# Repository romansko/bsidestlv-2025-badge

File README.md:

# BSidesTLV2025 Hardware CTF
Unlock the hidden secrets of the badge. What kind of secrets lie in waiting? Designed for security researchers and hardware enthusiasts, the BSidesTLV2025 badge is your ultimate mystery in digital exploration.

### About The Project
The BSidesTLV2025 badge is a hardware hacking challenge. It is suitable for both novice and experienced tinkerers and hackers. It utilizes a low number of components to make the challenge easier to grasp, but holds in itself enough intricacies that will require the challenger a keen eye and sharp mind to solve all challenges.

To solve the challenge you will need to discover a series of flags, hidden inside the badge. Each one will help you unlock the next step in the challenge, to finally reveal the ultimate secret the badge holds.

## How to Solve
You, as the challenger, will face a couple of tricks on the hardware level. It is strongly recommended to identify which chips are used, find their datasheet and understand how they are connected. Then, dive into the software to understand how it is built and figure out what needs to be done to make the badge uncover its truth to you. All the software (except the encryption keys and the flags) is available here on this repository. It is recommended to try and reverse engineer the PCB before heading towards the `hw` folder.

### Source structure
* `aes.cpp` [AES implementation](https://github.com/kokke/tiny-AES-c)
* `main.cpp` Boot and Setup

... The rest is up to you. :-)

### You Will Need
Ultimately, no additional tools are required to solve the challenges. However, for hardcore external hacking, the following list is a recommended list of equipment that is suggested to solve the challenge:
* Multimeter
* Soldering Iron
* Jumper wires
* An external microcontroller (Any Arduino/RPi)

### Software
Please install the following software to be able to flash software to the device:
* [ch32fun](https://github.com/cnlohr/ch32fun/wiki/Installation) Follow install guide for toolchain and `minichlink` flash utility
* [Flash Update](https://swordofsecrets.com/update.html) Use online update tool to update the sword using preflashed bootloader

### Hardware
All PCB specs are provided here under `hw/`. This can be easily manufactured as well as paneled for a larger volume. There are no special requirements for this board's manufacturing process.

#### Bill of Materials
| Quantity | Component Description | Datasheet |
|----------|-----------------------|-----------|
| 1 | CH32V003 RISC-V Microcontroller | [Datasheet](http://mcu.cz/images_articles/5007-CH32V003Reference-Manual.PDF) |
| 1 | AMS1117-3.3 LDO Voltage Regulator | [Datasheet](https://www.ti.com/lit/gpn/lm1117) |
| 1 | CH340N USB-toSerial | [Datasheet](https://cdn.sparkfun.com/assets/5/0/a/8/5/CH340DS1.PDF) |
| 1 | W25Q128JVSIQ 128MB NOR Flash | [Datasheet](https://www.mouser.co.il/datasheet/2/949/w25q128jv_revf_03272018_plus-1489608.pdf) |
| 1 | SMD 10 kOhms 0805 Resistor|  |
| 1 | SMD 100 kOhms 0805 Resistor |  |
| 3 | SMD 0.1 uF 0805 Capacitor |  |

<!-- LICENSE -->
## License

Distributed under the MIT License.

<p align="right">(<a href="#readme-top">back to top</a>)</p>

<!-- CONTACT -->
## Contact

Gili Yankovitch - [@GiliYankovitch](https://x.com/GiliYankovitch) - giliy@nyxsecurity.net

<!-- MARKDOWN LINKS & IMAGES -->
<!-- https://www.markdownguide.org/basic-syntax/#reference-style-links -->
[front]: images/front.png
[back]: images/back.png

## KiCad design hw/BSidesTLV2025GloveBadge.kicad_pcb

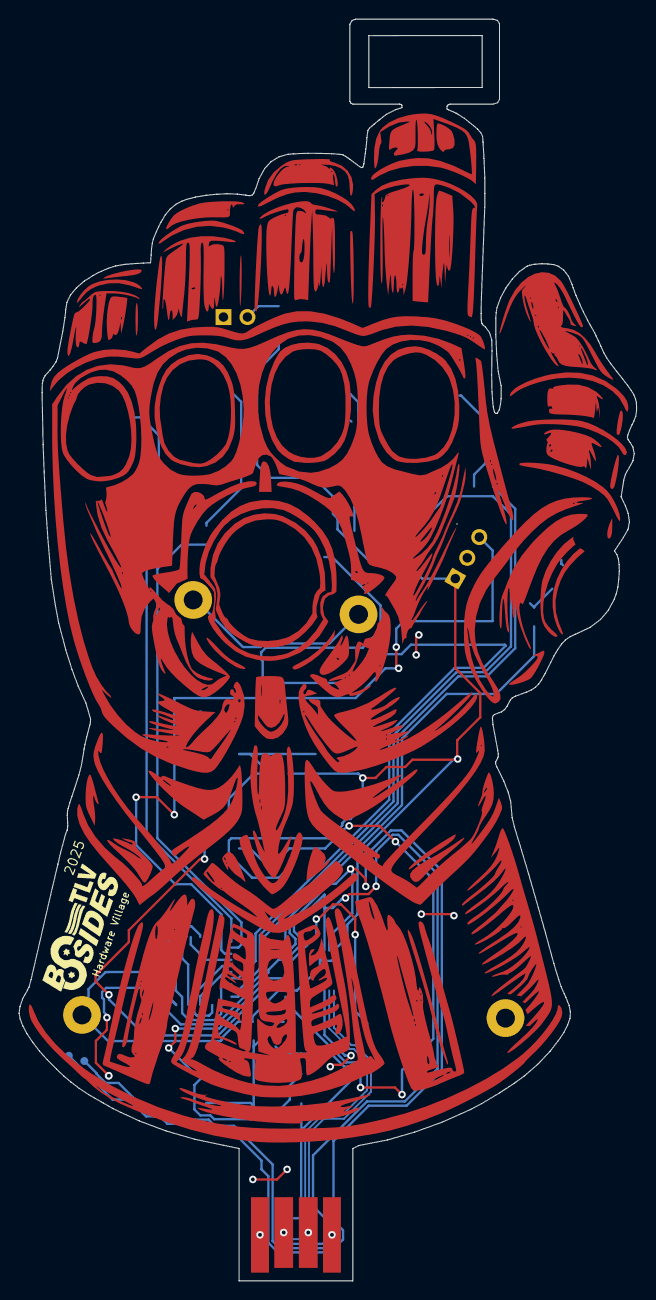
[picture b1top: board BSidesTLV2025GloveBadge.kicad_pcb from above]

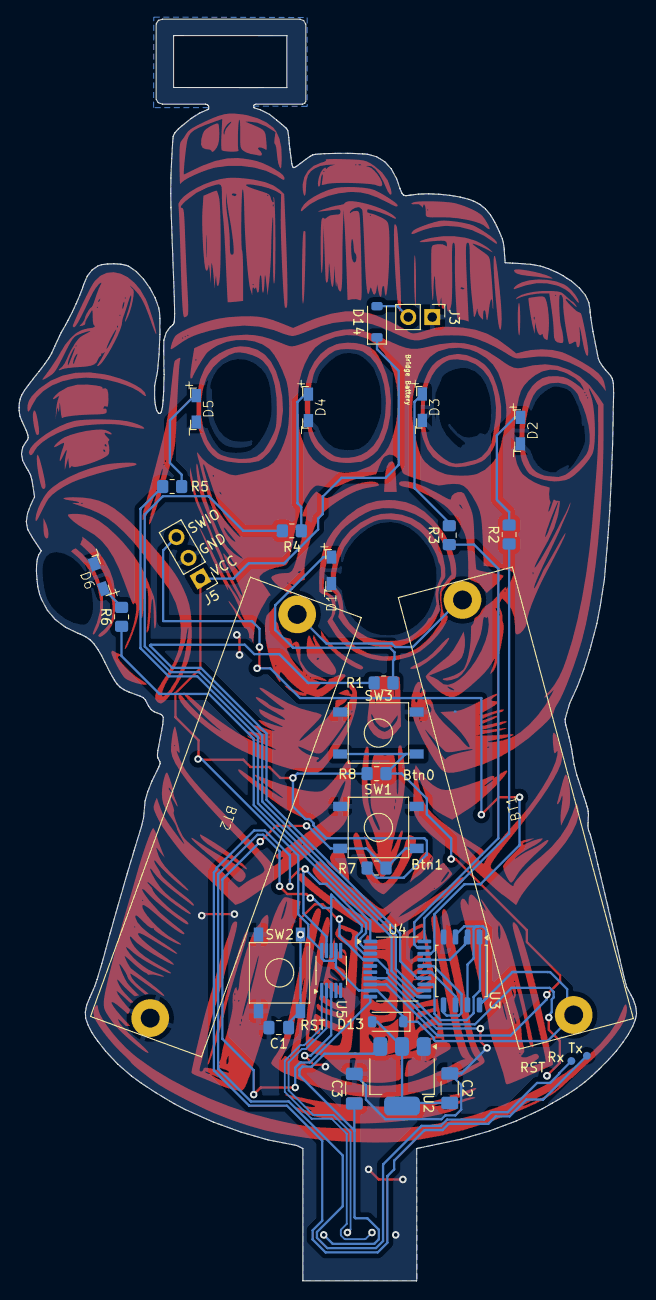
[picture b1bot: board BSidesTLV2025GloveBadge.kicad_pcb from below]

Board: 2 copper layers, 65.3 x 133.6 mm, 31 parts (30 on the bottom side), 30 nets.

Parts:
BT1, BT2: BATTERY-AAA; BH-AAA-A1AJ001
C1: 100nF; C_0805_2012Metric_Pad1.18x1.45mm_HandSolder
C2, C3: 100uF; C_1206_3216Metric_Pad1.33x1.80mm_HandSolder
D1, D2, D3, D4, D5, D6: LED; XL-2810
D13, D14: D; D_SOD-123
J2: USB_A; usb-PCB
J3: Conn_01x02_Pin; PinHeader_1x02_P2.54mm_Vertical
J5: Conn_01x03_Pin; PinHeader_1x03_P2.54mm_Vertical
R1, R2, R3, R4, R5, R6: 100; R_0805_2012Metric_Pad1.20x1.40mm_HandSolder
R7, R8: 1k; R_0805_2012Metric_Pad1.20x1.40mm_HandSolder
SW1, SW2, SW3: SW_Push; SMD-BTN-6x6-4Pin
U2: AMS1117-3.3; SOT-223-3_TabPin2
U3: W25Q128JVS; SOIC-8_5.23x5.23mm_P1.27mm
U4: CH32V003F4P6; TSSOP-20_4.4x6.5mm_P0.65mm
U5: CH340E; MSOP-10_3x3mm_P0.5mm

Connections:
3.3v: BT1.PWR@ (+), D13.1 (K), D14.1 (K), J5.1, R7.1, R8.1, U3.3 (IO2), U3.7 (IO3), U3.8 (VCC), U4.9 (VDD), U5.7 (VCC), U5.10 (V3)
D+: J2.3 (D+), U5.1 (UD+)
D-: J2.2 (D-), U5.2 (UD-)
GND: BT2.GND@ (-), C1.2, C2.1, C3.2, D1.1 (K), D2.1 (K), D3.1 (K), D4.1 (K), D5.1 (K), D6.1 (K), J2.4 (GND), J3.1, J5.2, SW1.1, SW2.1, SW3.1, U2.1 (GND), U3.4 (GND), U4.7 (VSS), U5.3 (GND)
MISO: U3.2 (DO(IO1)), U4.17 (PC7)
MOSI: U3.5 (DI(IO0)), U4.16 (PC6)
unnamed: BT1.GND@ (-), BT2.PWR@ (+)
unnamed: D1.2 (A), R1.2
unnamed: D2.2 (A), R2.2
unnamed: D3.2 (A), R3.2
unnamed: D4.2 (A), R4.2
unnamed: D5.2 (A), R5.2
unnamed: D6.2 (A), R6.2
unnamed: C2.2, D13.2 (A), U2.2 (VO)
unnamed: D14.2 (A), J3.2
PC0: R7.2, SW1.2, U4.10 (PC0)
PC1: R5.1, U4.11 (PC1)
PC2: R4.1, U4.12 (PC2)
PC3: U3.1 (~CS), U4.13 (PC3)
PC4: R1.1, U4.14 (PC4)
PD0: R8.2, SW3.2, U4.8 (PD0)
PD2: R3.1, U4.19 (PD2)
PD3: R2.1, U4.20 (PD3)
PD4: R6.1, U4.1 (PD4)
RST: C1.1, SW2.2, U4.4 (NRST/PD7)
RX: U4.3 (PD6), U5.8 (TXD)
RXOUT: U4.2 (PD5), U5.9 (RXD)
SCK: U3.6 (CLK), U4.15 (PC5)
SWIO: J5.3, U4.18 (PD1)
VCC: C3.1, J2.1 (VBUS), U2.3 (VI)

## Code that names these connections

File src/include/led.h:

#ifndef LED_H
#define LED_H

#include <stdint.h>
#include <ch32v003fun.h>

// LED pin definitions
#define PIN_HAND_LED PC4
#define PIN_THUMB_LED PD4
#define PIN_LITTLE_LED PD3
#define PIN_RING_LED PD2
#define PIN_MIDDLE_LED PC2
#define PIN_INDEX_LED PC1

// LED state bit positions
#define LED_STATE_LITTLE 0
#define LED_STATE_RING   1
#define LED_STATE_MIDDLE 2
#define LED_STATE_INDEX  3
#define LED_STATE_THUMB  4
#define LED_STATE_HAND   5

// LED control functions
void led_init(void);
void turn_on_led(int pin);
void turn_off_led(int pin);
void toggle_led(int pin, int led_bit);
void blink_finger(int pin, int n);
void blink_finger_custom_delay(int pin, int n, int delay);
void blink_fingers_in_sequence(void);
void turn_off_all_leds(void);
void boot_sequence(int _delay);
void blink_all_leds(int n);
int are_all_leds_on(void);
void handle_led_challenge(uint8_t value);
void challenge_success(int pin);
void challenge_failure(int pin);
void all_challenges_success(void);
#endif // LED_H

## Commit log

2025-11-10 init
2025-11-10 increased speed of all_challenges_success animation (now 300ms - was 1000ms)
2025-11-24 Add LED fill minigame with automatic restart on failure
    This commit introduces a new interactive minigame where users must hold
    a button and release it precisely when all 6 LEDs are lit.
    Features:
    - LED Fill Minigame: Players hold BTN_0 while LEDs fill sequentially
    (LITTLE, RING, MIDDLE, INDEX, THUMB, HAND) with 100ms delay between each
    - Timing Challenge: Goal is to release the button when all 6 LEDs are lit
2025-11-24 Add configurable fill rate and progressive difficulty minigame mode
    This commit enhances the LED fill minigame with configurable difficulty
    levels and a progressive challenge mode that tests players across multiple
    speed settings.
    Key Features:
    - Configurable Fill Rate: minigame now accepts fill_rate_ms parameter
    to control LED fill speed (replaces hardcoded 100ms delay)
2025-12-10 chore: Fixing README
2025-12-11 chore: Fixing commands action
2025-12-13 chore: Updating the schematics to the accurate glove hw
